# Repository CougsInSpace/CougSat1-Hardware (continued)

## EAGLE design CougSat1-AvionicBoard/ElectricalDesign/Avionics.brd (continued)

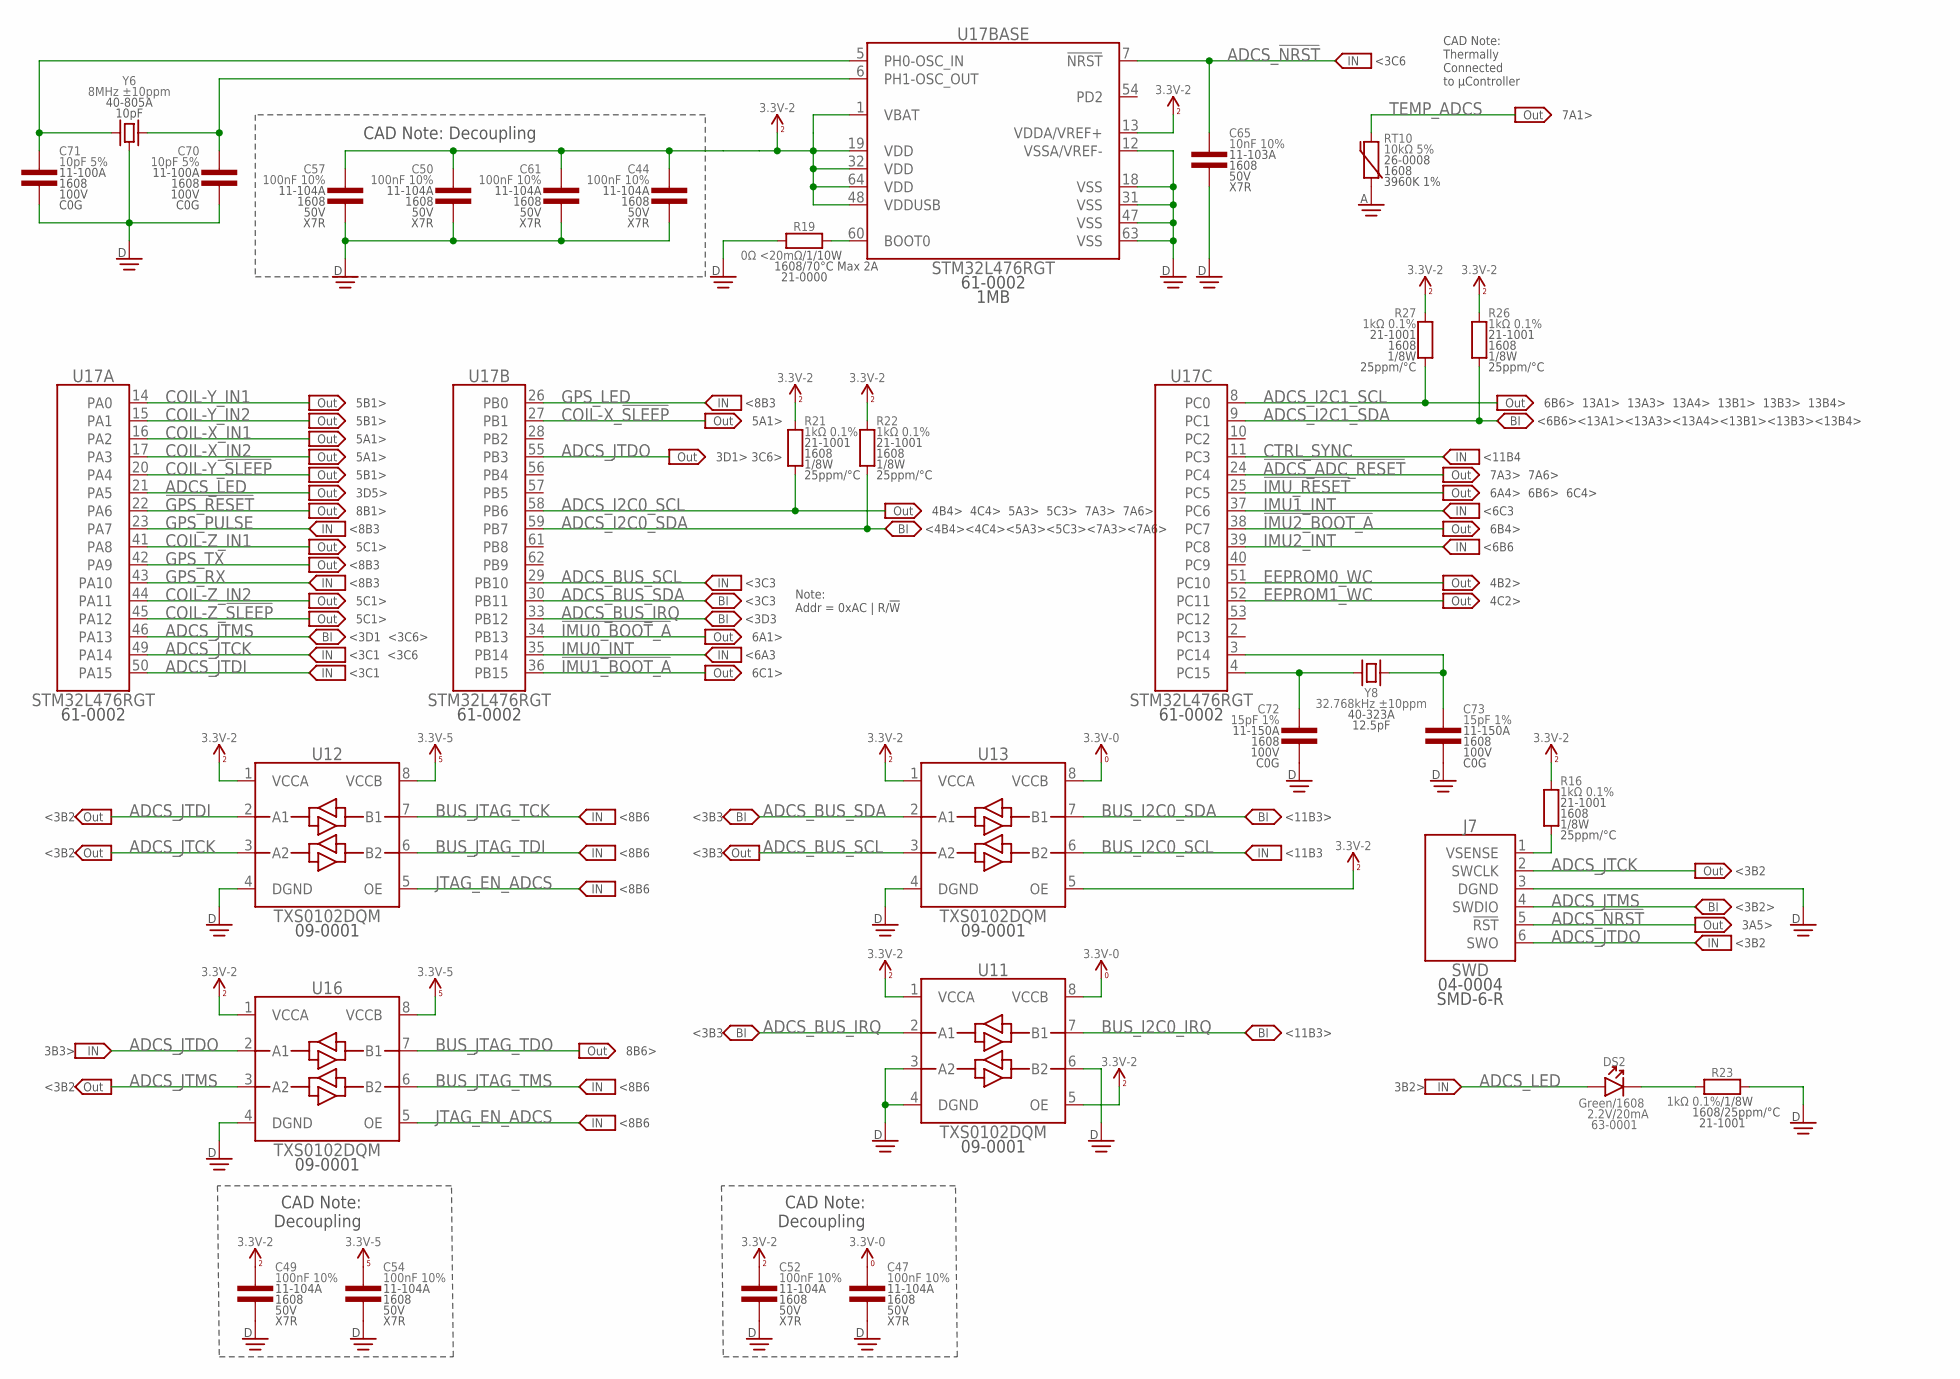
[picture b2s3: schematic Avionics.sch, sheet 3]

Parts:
C44, C47, C49, C50, C52, C54, C57, C61: 100nF 10%; 1608
C65: 10nF 10%; 1608
C70, C71: 10pF 5%; 1608
C72, C73: 15pF 1%; 1608
DS2: Green; 1608-POL
J7: SWD; SMD2.54-1X06-R
R16, R21, R22, R23, R26, R27: 1kΩ 0.1%; 1608
R19: 0Ω <20mΩ; 1608
RT10: 10kΩ 5%; 1608
U11, U12, U13, U16: TXS0102DQM; X2SON-8
U17: STM32L476RGT; QFP-64-1010
Y6: 8MHz ±10ppm; SMD-5032
Y8: 32.768kHz ±10ppm; SMD-3215

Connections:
3.3V_0: C47.1, U11.8 (VCCB), U13.8 (VCCB); also elsewhere on the board
3.3V_2: C44.1, C49.1, C50.1, C52.1, C57.1, C61.1, R16.2, R21.2, R22.2, R26.2, R27.2, U11.1 (VCCA), U11.5 (OE), U12.1 (VCCA), U13.1 (VCCA), U13.5 (OE), U16.1 (VCCA), U17.1 (VBAT), U17.13 (VDDA/VREF+), U17.19 (VDD), U17.32 (VDD), U17.48 (VDDUSB), U17.64 (VDD); also elsewhere on the board
3.3V_5: C54.1, U12.8 (VCCB), U16.8 (VCCB); also elsewhere on the board
!ADCS_ADC_RESET!: U17.24 (PC4); also elsewhere on the board
!GPS_RESET: U17.22 (PA6); also elsewhere on the board
!IMU0_BOOT_A: U17.34 (PB13); also elsewhere on the board
!IMU1_BOOT_A: U17.36 (PB15); also elsewhere on the board
!IMU2_BOOT_A: U17.38 (PC7); also elsewhere on the board
!IMU_RESET: U17.25 (PC5); also elsewhere on the board
ADCS_!NRST: C65.1, J7.5 (!RST), U17.7 (!NRST)
ADCS_BOOT0: R19.2, U17.60 (BOOT0)
ADCS_BUS_IRQ: U11.2 (A1), U17.33 (PB12)
ADCS_BUS_SCL: U13.3 (A2), U17.29 (PB10)
ADCS_BUS_SDA: U13.2 (A1), U17.30 (PB11)
ADCS_I2C0_SCL: R21.1, U17.58 (PB6); also elsewhere on the board
ADCS_I2C0_SDA: R22.1, U17.59 (PB7); also elsewhere on the board
ADCS_I2C1_SCL: R27.1, U17.8 (PC0); also elsewhere on the board
ADCS_I2C1_SDA: R26.1, U17.9 (PC1); also elsewhere on the board
ADCS_JTCK: J7.2 (SWCLK), U12.3 (A2), U17.49 (PA14)
ADCS_JTDI: U12.2 (A1), U17.50 (PA15)
ADCS_JTDO: J7.6 (SWO), U16.2 (A1), U17.55 (PB3)
ADCS_JTMS: J7.4 (SWDIO), U16.3 (A2), U17.46 (PA13)
ADCS_LED: DS2.A, U17.21 (PA5)
ADCS_LED_GND: DS2.C, R23.1
ADCS_OSC_32_IN: C72.1, U17.4 (PC15), Y8.1
ADCS_OSC_32_OUT: C73.1, U17.3 (PC14), Y8.2
ADCS_OSC_IN: C71.1, U17.5 (PH0-OSC_IN), Y6.1
ADCS_OSC_OUT: C70.1, U17.6 (PH1-OSC_OUT), Y6.3 (2)
ADCS_SWD_VSENCE: J7.1 (VSENSE), R16.1
AGND: RT10.1; also elsewhere on the board
BUS_I2C0_IRQ: U11.7 (B1); also elsewhere on the board
BUS_I2C0_SCL: U13.6 (B2); also elsewhere on the board
BUS_I2C0_SDA: U13.7 (B1); also elsewhere on the board
BUS_JTAG_TCK: U12.7 (B1); also elsewhere on the board
BUS_JTAG_TDI: U12.6 (B2); also elsewhere on the board
BUS_JTAG_TDO: U16.7 (B1); also elsewhere on the board
BUS_JTAG_TMS: U16.6 (B2); also elsewhere on the board
COIL-X_!SLEEP: U17.27 (PB1); also elsewhere on the board
COIL-X_IN1: U17.16 (PA2); also elsewhere on the board
COIL-X_IN2: U17.17 (PA3); also elsewhere on the board
COIL-Y_!SLEEP: U17.20 (PA4); also elsewhere on the board
COIL-Y_IN1: U17.14 (PA0); also elsewhere on the board
COIL-Y_IN2: U17.15 (PA1); also elsewhere on the board
COIL-Z_!SLEEP: U17.45 (PA12); also elsewhere on the board
COIL-Z_IN1: U17.41 (PA8); also elsewhere on the board
COIL-Z_IN2: U17.44 (PA11); also elsewhere on the board
CTRL_SYNC: U17.11 (PC3); also elsewhere on the board
DGND: C44.2, C47.2, C49.2, C50.2, C52.2, C54.2, C57.2, C61.2, C65.2, C70.2, C71.2, C72.2, C73.2, J7.3 (DGND), R19.1, R23.2, U11.3 (A2), U11.4 (DGND), U11.6 (B2), U12.4 (DGND), U13.4 (DGND), U16.4 (DGND), U17.12 (VSSA/VREF-), U17.18 (VSS), U17.31 (VSS), U17.47 (VSS), U17.63 (VSS), Y6.2 (GND), Y6.4 (GND); also elsewhere on the board
EEPROM0_WC: U17.51 (PC10); also elsewhere on the board
EEPROM1_WC: U17.52 (PC11); also elsewhere on the board
GPS_LED: U17.26 (PB0); also elsewhere on the board
GPS_PULSE: U17.23 (PA7); also elsewhere on the board
GPS_RX: U17.43 (PA10); also elsewhere on the board
GPS_TX: U17.42 (PA9); also elsewhere on the board
IMU0_INT: U17.35 (PB14); also elsewhere on the board
IMU1_INT: U17.37 (PC6); also elsewhere on the board
IMU2_INT: U17.39 (PC8); also elsewhere on the board
JTAG_EN_ADCS: U12.5 (OE), U16.5 (OE); also elsewhere on the board
TEMP_ADCS: RT10.2; also elsewhere on the board

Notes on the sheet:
5C1>
8B1>
<8B3
3D1> 3C6>
<3B2
<3B2>
4B4> 4C4> 5A3> 5C3> 7A3> 7A6>
<4B4><4C4><5A3><5C3><7A3><7A6>
<11B3>
6A1>
<6A3
6C1>
<6C3
6B4>
<6B6
4B2>
4C2>
6B6> 13A1> 13A3> 13A4> 13B1> 13B3> 13B4>
<6B6><13A1><13A3><13A4><13B1><13B3><13B4>
<3B2
3B3>
<8B6
8B6>
CAD Note: Thermally Connected to µController
7A1>
3A5>
3D5>
3B2>
CAD Note: Decoupling
CAD Note: Decoupling
Note: Addr = 0xAC | R/!W!
<11B4
6A4> 6B6> 6C4>
7A3> 7A6>
<3B3
<3D1 <3C6>
<3C1 <3C6
<3C1
<3C3
<3D3

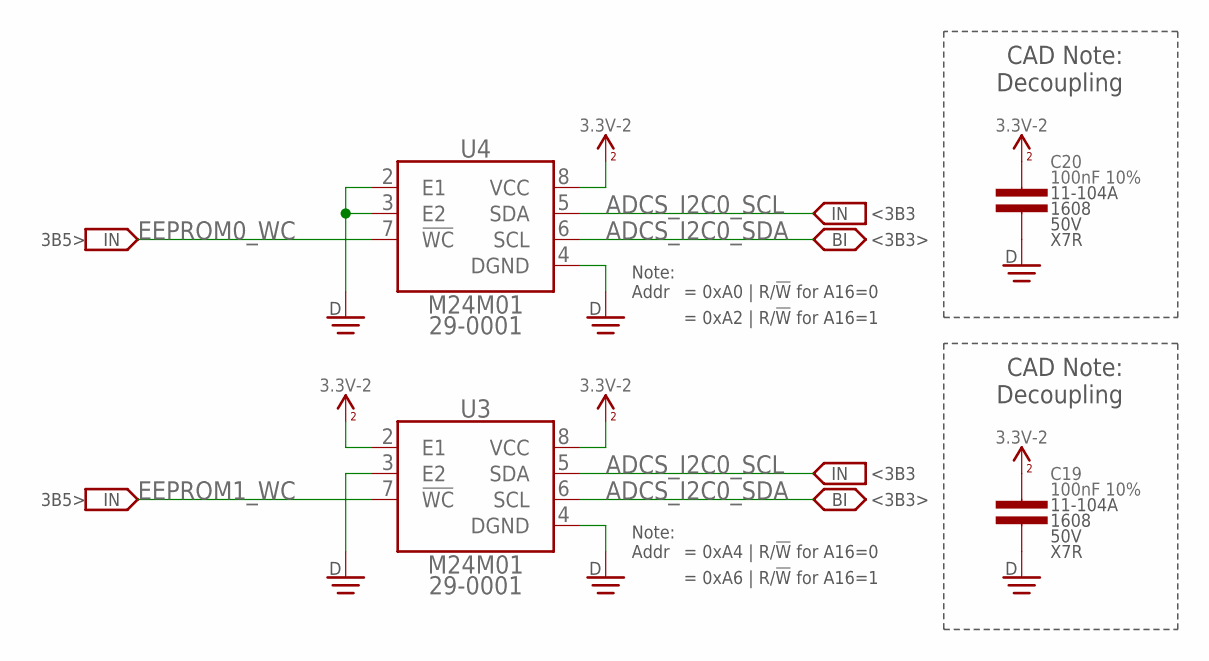
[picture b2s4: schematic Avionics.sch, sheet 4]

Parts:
C19, C20: 100nF 10%; 1608
U3, U4: M24M01; SO8

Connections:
3.3V_2: C19.1, C20.1, U3.2 (E1), U3.8 (VCC), U4.8 (VCC); also elsewhere on the board
ADCS_I2C0_SCL: U3.5 (SDA), U4.5 (SDA); also elsewhere on the board
ADCS_I2C0_SDA: U3.6 (SCL), U4.6 (SCL); also elsewhere on the board
DGND: C19.2, C20.2, U3.3 (E2), U3.4 (DGND), U4.2 (E1), U4.3 (E2), U4.4 (DGND); also elsewhere on the board
EEPROM0_WC: U4.7 (!WC); also elsewhere on the board
EEPROM1_WC: U3.7 (!WC); also elsewhere on the board

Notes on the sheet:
<3B3>
<3B3
3B5>
CAD Note: Decoupling
Note: Addr
= 0xA2 | R/!W! for A16=1
= 0xA0 | R/!W! for A16=0
= 0xA6 | R/!W! for A16=1
= 0xA4 | R/!W! for A16=0

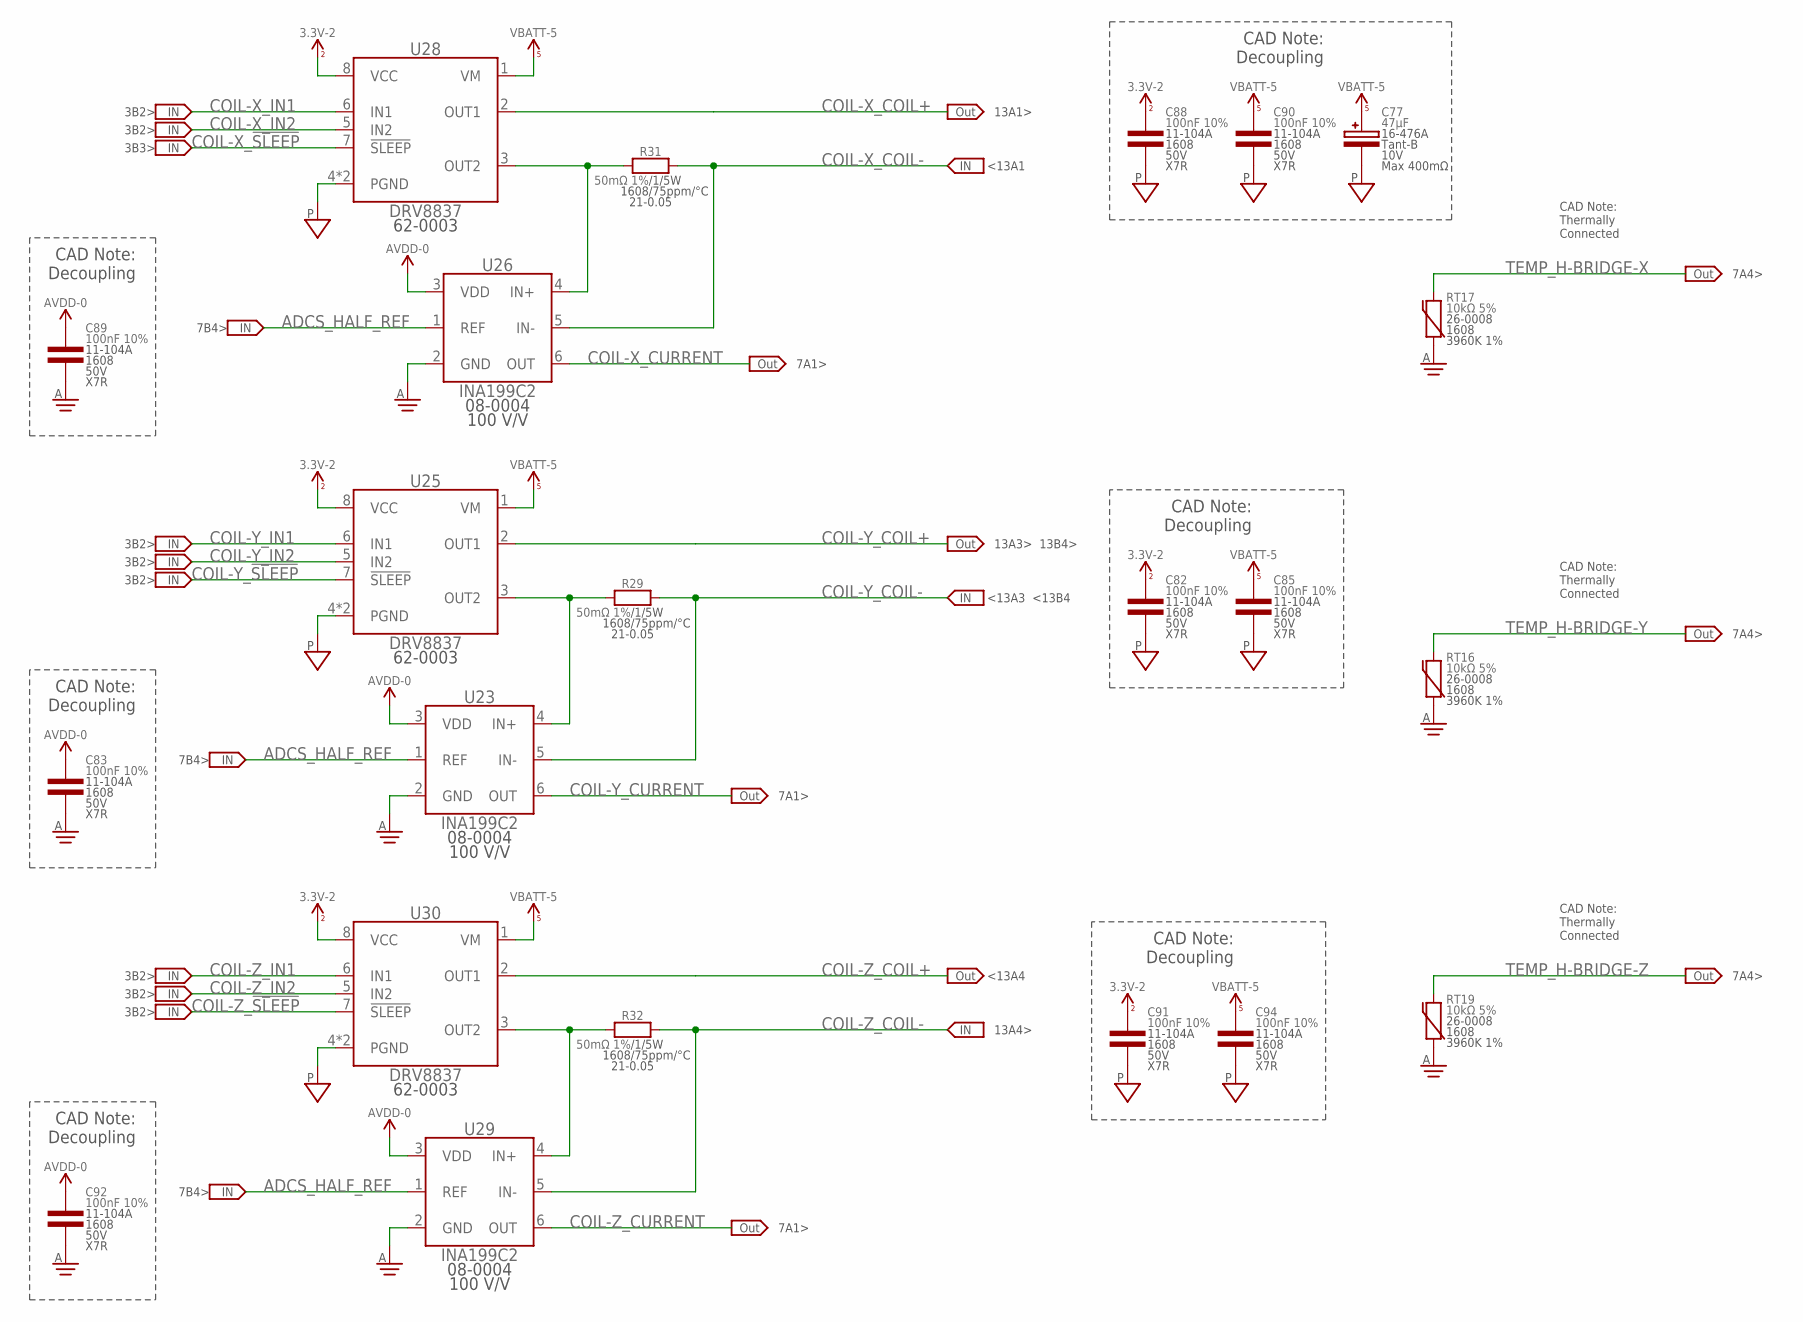
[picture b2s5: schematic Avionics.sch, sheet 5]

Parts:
C77: 47µF; 4028-POL
C82, C83, C85, C88, C89, C90, C91, C92, C94: 100nF 10%; 1608
R29, R31, R32: 50mΩ 1%; 1608
RT16, RT17, RT19: 10kΩ 5%; 1608
U23, U26, U29: INA199C2; SOT363
U25, U28, U30: DRV8837; WSON-8

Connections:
3.3V_2: C82.1, C88.1, C91.1, U25.8 (VCC), U28.8 (VCC), U30.8 (VCC); also elsewhere on the board
ADCS_HALF_REF: U23.1 (REF), U26.1 (REF), U29.1 (REF); also elsewhere on the board
AGND: C83.2, C89.2, C92.2, RT16.1, RT17.1, RT19.1, U23.2 (GND), U26.2 (GND), U29.2 (GND); also elsewhere on the board
AVDD-0: C83.1, C89.1, C92.1, U23.3 (VDD), U26.3 (VDD), U29.3 (VDD); also elsewhere on the board
COIL-X_!SLEEP: U28.7 (!SLEEP); also elsewhere on the board
COIL-X_COIL+: U28.2 (OUT1); also elsewhere on the board
COIL-X_COIL-: R31.2, U26.5 (IN-); also elsewhere on the board
COIL-X_CURRENT: U26.6 (OUT); also elsewhere on the board
COIL-X_IN1: U28.6 (IN1); also elsewhere on the board
COIL-X_IN2: U28.5 (IN2); also elsewhere on the board
COIL-X_OUT2: R31.1, U26.4 (IN+), U28.3 (OUT2)
COIL-Y_!SLEEP: U25.7 (!SLEEP); also elsewhere on the board
COIL-Y_COIL+: U25.2 (OUT1); also elsewhere on the board
COIL-Y_COIL-: R29.2, U23.5 (IN-); also elsewhere on the board
COIL-Y_CURRENT: U23.6 (OUT); also elsewhere on the board
COIL-Y_IN1: U25.6 (IN1); also elsewhere on the board
COIL-Y_IN2: U25.5 (IN2); also elsewhere on the board
COIL-Y_OUT2: R29.1, U23.4 (IN+), U25.3 (OUT2)
COIL-Z_!SLEEP: U30.7 (!SLEEP); also elsewhere on the board
COIL-Z_COIL+: U30.2 (OUT1); also elsewhere on the board
COIL-Z_COIL-: R32.2, U29.5 (IN-); also elsewhere on the board
COIL-Z_CURRENT: U29.6 (OUT); also elsewhere on the board
COIL-Z_IN1: U30.6 (IN1); also elsewhere on the board
COIL-Z_IN2: U30.5 (IN2); also elsewhere on the board
COIL-Z_OUT2: R32.1, U29.4 (IN+), U30.3 (OUT2)
PGND: C77.C, C82.2, C85.2, C88.2, C90.2, C91.2, C94.2, U25.4 (PGND), U25.PAD (PGND), U28.4 (PGND), U28.PAD (PGND), U30.4 (PGND), U30.PAD (PGND); also elsewhere on the board
TEMP_H-BRIDGE-X: RT17.2; also elsewhere on the board
TEMP_H-BRIDGE-Y: RT16.2; also elsewhere on the board
TEMP_H-BRIDGE-Z: RT19.2; also elsewhere on the board
VBATT_5: C77.A, C85.1, C90.1, C94.1, U25.1 (VM), U28.1 (VM), U30.1 (VM); also elsewhere on the board

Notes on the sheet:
CAD Note: Thermally Connected
7A4>
CAD Note: Decoupling
7B4>
7A1>
3B2>
13A1>
<13A1
3B3>
13A3> 13B4>
<13A3 <13B4
13A4>
<13A4

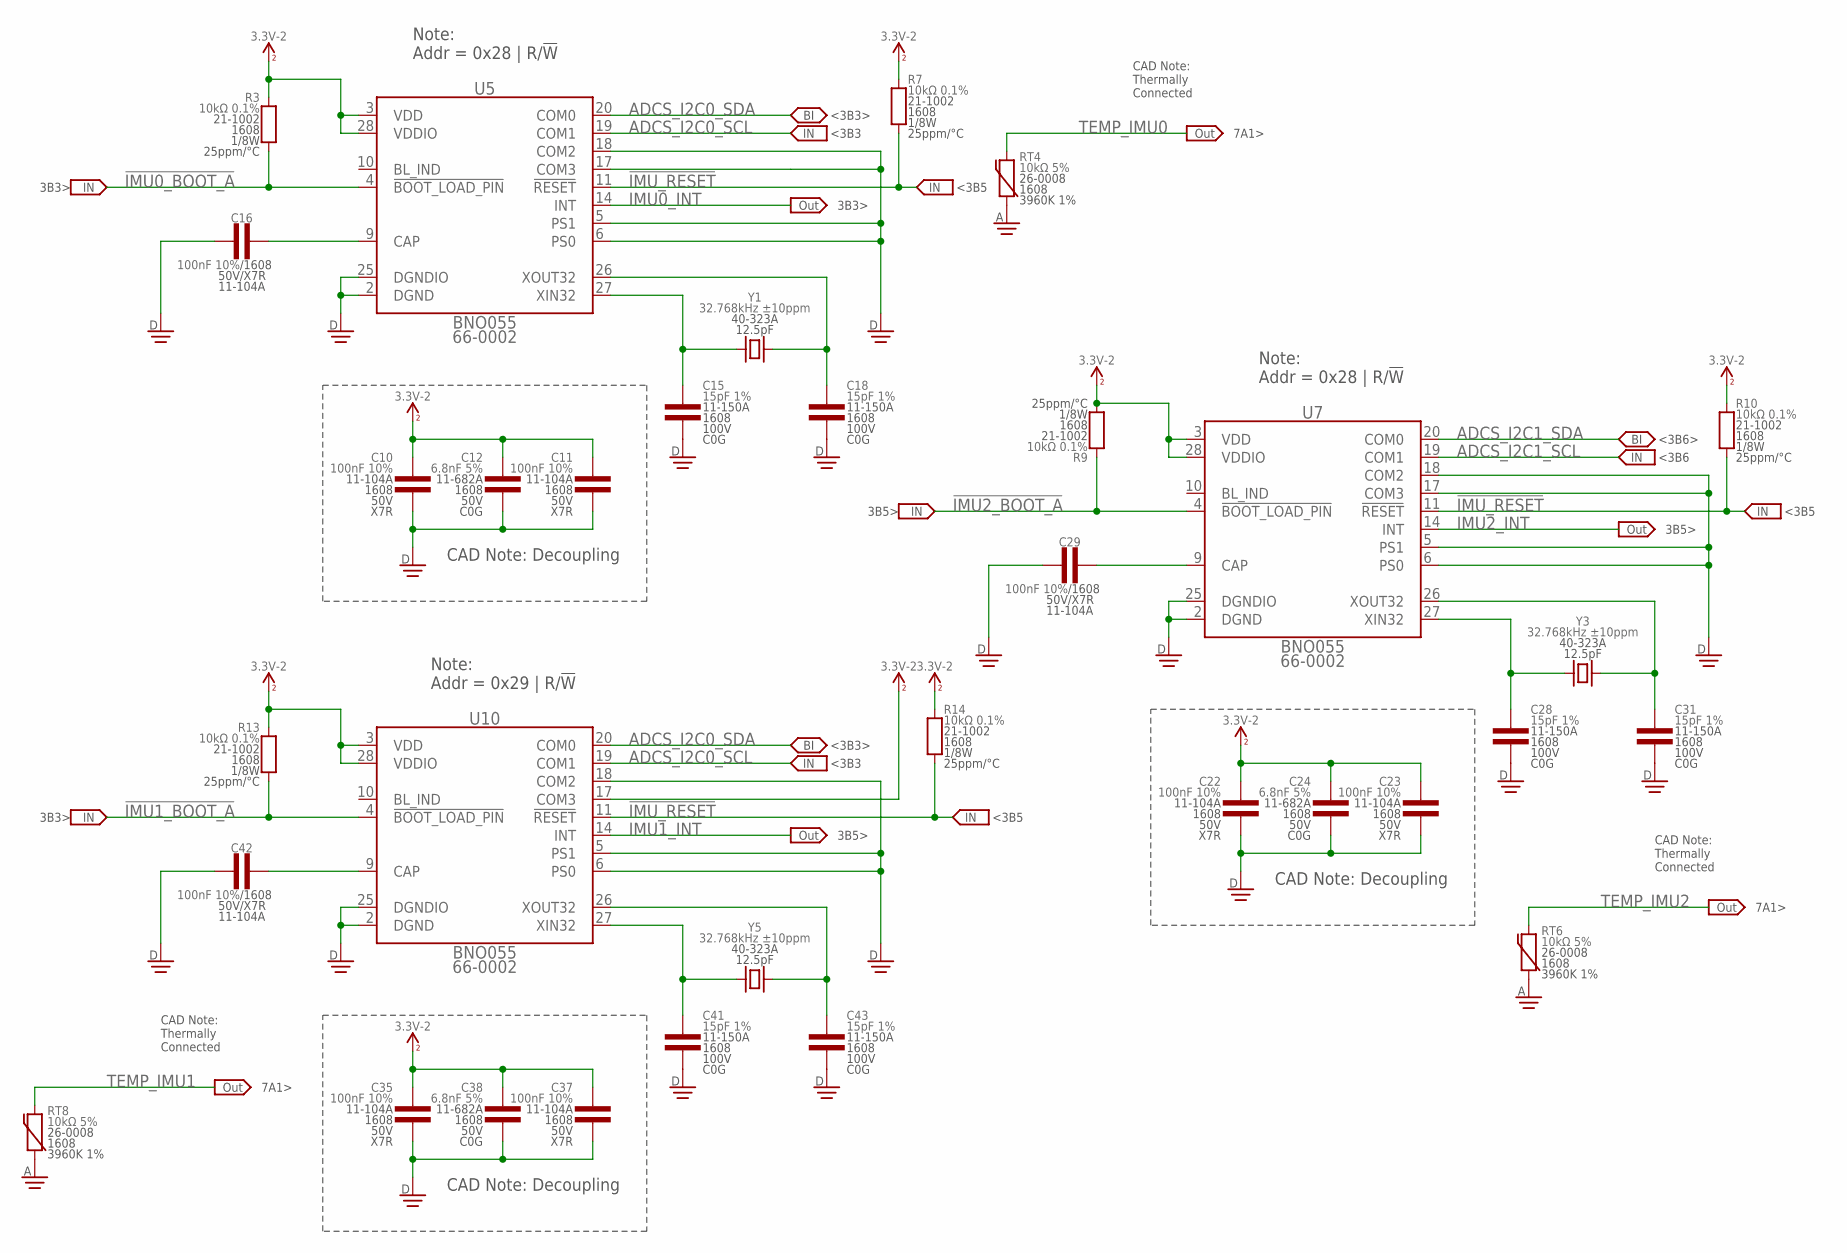
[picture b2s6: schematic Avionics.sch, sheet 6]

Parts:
C10, C11, C16, C22, C23, C29, C35, C37, C42: 100nF 10%; 1608
C12, C24, C38: 6.8nF 5%; 1608
C15, C18, C28, C31, C41, C43: 15pF 1%; 1608
R3, R7, R9, R10, R13, R14: 10kΩ 0.1%; 1608
RT4, RT6, RT8: 10kΩ 5%; 1608
U5, U7, U10: BNO055; LGA-28-4050
Y1, Y3, Y5: 32.768kHz ±10ppm; SMD-3215

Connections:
3.3V_2: C10.1, C11.1, C12.1, C22.1, C23.1, C24.1, C35.1, C37.1, C38.1, R3.2, R7.2, R9.1, R10.2, R13.2, R14.2, U5.3 (VDD), U5.28 (VDDIO), U7.3 (VDD), U7.28 (VDDIO), U10.3 (VDD), U10.17 (COM3), U10.28 (VDDIO); also elsewhere on the board
!IMU0_BOOT_A: R3.1, U5.4 (!BOOT_LOAD_PIN); also elsewhere on the board
!IMU1_BOOT_A: R13.1, U10.4 (!BOOT_LOAD_PIN); also elsewhere on the board
!IMU2_BOOT_A: R9.2, U7.4 (!BOOT_LOAD_PIN); also elsewhere on the board
!IMU_RESET: R7.1, R10.1, R14.1, U5.11 (!RESET), U7.11 (!RESET), U10.11 (!RESET); also elsewhere on the board
ADCS_I2C0_SCL: U5.19 (COM1), U10.19 (COM1); also elsewhere on the board
ADCS_I2C0_SDA: U5.20 (COM0), U10.20 (COM0); also elsewhere on the board
ADCS_I2C1_SCL: U7.19 (COM1); also elsewhere on the board
ADCS_I2C1_SDA: U7.20 (COM0); also elsewhere on the board
ADCS_IMU1_OSC_32_IN: C41.1, U10.27 (XIN32), Y5.2
ADCS_IMU1_OSC_32_IN1: C15.1, U5.27 (XIN32), Y1.2
ADCS_IMU1_OSC_32_IN2: C28.1, U7.27 (XIN32), Y3.2
ADCS_IMU1_OSC_32_OUT: C43.1, U10.26 (XOUT32), Y5.1
ADCS_IMU1_OSC_32_OUT1: C18.1, U5.26 (XOUT32), Y1.1
ADCS_IMU1_OSC_32_OUT2: C31.1, U7.26 (XOUT32), Y3.1
AGND: RT4.1, RT6.1, RT8.1; also elsewhere on the board
DGND: C10.2, C11.2, C12.2, C15.2, C16.1, C18.2, C22.2, C23.2, C24.2, C28.2, C29.1, C31.2, C35.2, C37.2, C38.2, C41.2, C42.1, C43.2, U5.2 (DGND), U5.5 (PS1), U5.6 (PS0), U5.17 (COM3), U5.18 (COM2), U5.25 (DGNDIO), U7.2 (DGND), U7.5 (PS1), U7.6 (PS0), U7.17 (COM3), U7.18 (COM2), U7.25 (DGNDIO), U10.2 (DGND), U10.5 (PS1), U10.6 (PS0), U10.18 (COM2), U10.25 (DGNDIO); also elsewhere on the board
IMU0_CAP: C16.2, U5.9 (CAP)
IMU0_INT: U5.14 (INT); also elsewhere on the board
IMU1_CAP: C42.2, U10.9 (CAP)
IMU1_INT: U10.14 (INT); also elsewhere on the board
IMU2_CAP: C29.2, U7.9 (CAP)
IMU2_INT: U7.14 (INT); also elsewhere on the board
TEMP_IMU0: RT4.2; also elsewhere on the board
TEMP_IMU1: RT8.2; also elsewhere on the board
TEMP_IMU2: RT6.2; also elsewhere on the board

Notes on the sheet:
CAD Note: Decoupling
<3B3>
<3B3
3B3>
3B3>
3B5>
3B5>
<3B6>
<3B6
CAD Note: Thermally Connected
7A1>
Note: Addr = 0x28 | R/!W
Note: Addr = 0x29 | R/!W
<3B5

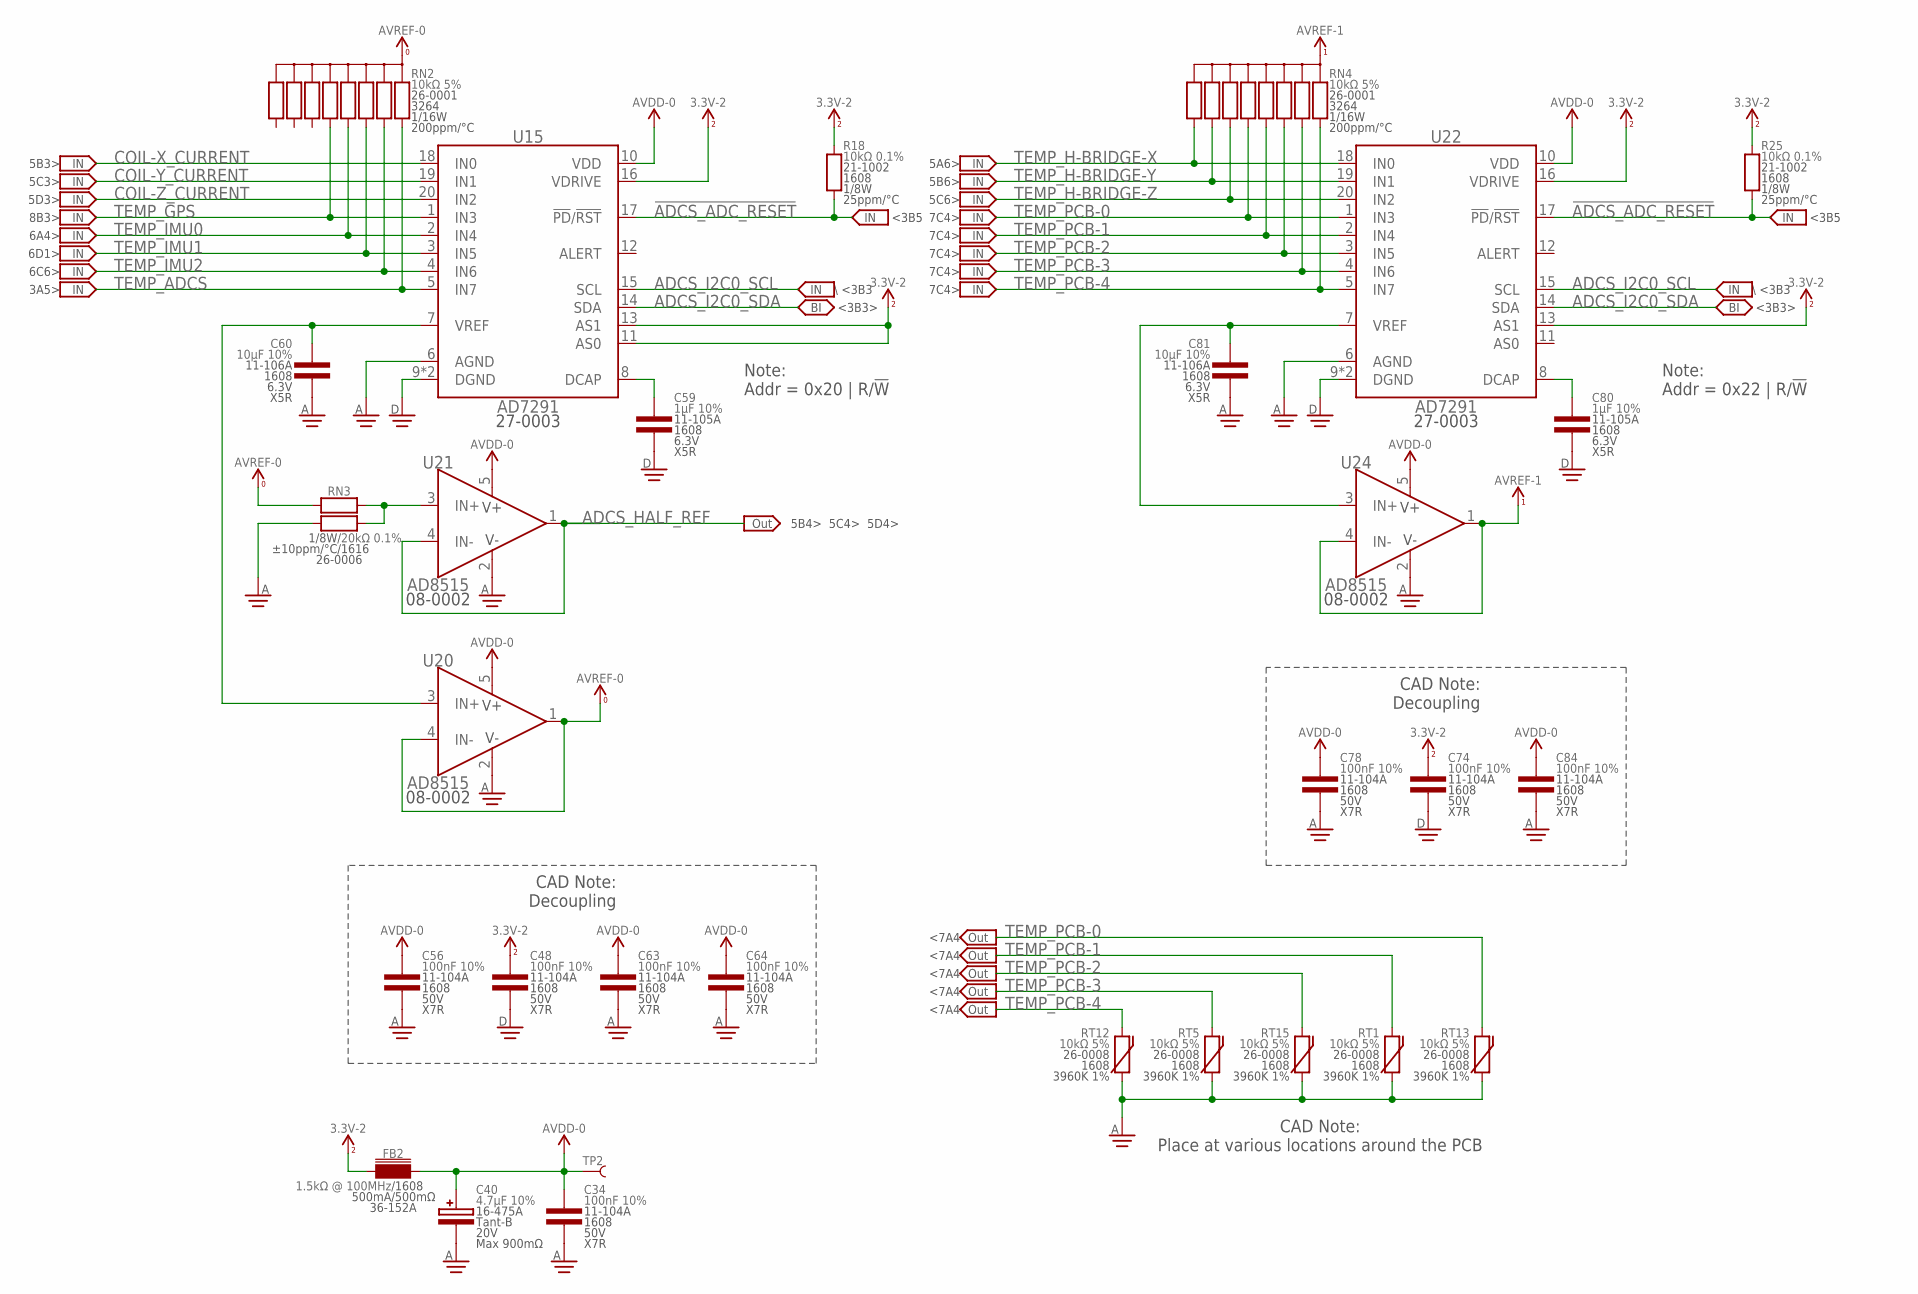
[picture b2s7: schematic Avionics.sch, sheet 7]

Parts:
C34, C48, C56, C63, C64, C74, C78, C84: 100nF 10%; 1608
C40: 4.7µF 10%; 4028-POL
C59, C80: 1µF 10%; 1608
C60, C81: 10µF 10%; 1608
FB2: 1.5kΩ @ 100MHz; 1608
R18, R25: 10kΩ 0.1%; 1608
RN2, RN4: 10kΩ 5%; 3264
RN3: 20kΩ 0.1%; 1616
RT1, RT5, RT12, RT13, RT15: 10kΩ 5%; 1608
TP2: TEST_POINT-SMD-C-1.25; SMD-C-1.25
U15, U22: AD7291; QFN-20-4040
U20, U21, U24: AD8515; SOT23-5

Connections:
3.3V_2: C48.1, C74.1, FB2.1, R18.2, R25.2, U15.11 (AS0), U15.13 (AS1), U15.16 (VDRIVE), U22.13 (AS1), U22.16 (VDRIVE); also elsewhere on the board
!ADCS_ADC_RESET!: R18.1, R25.1, U15.17 (!PD!/!RST), U22.17 (!PD!/!RST); also elsewhere on the board
ADCS_ADC0_DCAP: C59.1, U15.8 (DCAP)
ADCS_ADC0_VREF: C60.1, U15.7 (VREF), U20.3 (IN+)
ADCS_ADC1_DCAP: C80.1, U22.8 (DCAP)
ADCS_ADC1_VREF: C81.1, U22.7 (VREF), U24.3 (IN+)
ADCS_HALF_REF: U21.1 (OUT), U21.4 (IN-); also elsewhere on the board
ADCS_HALF_REF_UNBUFF: RN3.1 (A1), RN3.2 (B1), U21.3 (IN+)
ADCS_I2C0_SCL: U15.15 (SCL), U22.15 (SCL); also elsewhere on the board
ADCS_I2C0_SDA: U15.14 (SDA), U22.14 (SDA); also elsewhere on the board
AGND: C34.2, C40.C, C56.2, C60.2, C63.2, C64.2, C78.2, C81.2, C84.2, RN3.4 (A2), RT1.1, RT5.1, RT12.1, RT13.1, RT15.1, U15.6 (AGND), U20.2 (V-), U21.2 (V-), U22.6 (AGND), U24.2 (V-); also elsewhere on the board
AVDD-0: C34.1, C40.A, C56.1, C63.1, C64.1, C78.1, C84.1, FB2.2, TP2.1, U15.10 (VDD), U20.5 (V+), U21.5 (V+), U22.10 (VDD), U24.5 (V+); also elsewhere on the board
AVREF-0: RN2.5 (C), RN2.10 (C), RN3.3 (B2), U20.1 (OUT), U20.4 (IN-)
AVREF-1: RN4.5 (C), RN4.10 (C), U24.1 (OUT), U24.4 (IN-)
COIL-X_CURRENT: U15.18 (IN0); also elsewhere on the board
COIL-Y_CURRENT: U15.19 (IN1); also elsewhere on the board
COIL-Z_CURRENT: U15.20 (IN2); also elsewhere on the board
DGND: C48.2, C59.2, C74.2, C80.2, U15.9 (DGND), U15.PAD (DGND), U22.9 (DGND), U22.PAD (DGND); also elsewhere on the board
TEMP_ADCS: RN2.1, U15.5 (IN7); also elsewhere on the board
TEMP_GPS: RN2.6 (5), U15.1 (IN3); also elsewhere on the board
TEMP_H-BRIDGE-X: RN4.9 (8), U22.18 (IN0); also elsewhere on the board
TEMP_H-BRIDGE-Y: RN4.8 (7), U22.19 (IN1); also elsewhere on the board
TEMP_H-BRIDGE-Z: RN4.7 (6), U22.20 (IN2); also elsewhere on the board
TEMP_IMU0: RN2.4, U15.2 (IN4); also elsewhere on the board
TEMP_IMU1: RN2.3, U15.3 (IN5); also elsewhere on the board
TEMP_IMU2: RN2.2, U15.4 (IN6); also elsewhere on the board
TEMP_PCB-0: RN4.6 (5), RT13.2, U22.1 (IN3)
TEMP_PCB-1: RN4.4, RT1.2, U22.2 (IN4)
TEMP_PCB-2: RN4.3, RT15.2, U22.3 (IN5)
TEMP_PCB-3: RN4.2, RT5.2, U22.4 (IN6)
TEMP_PCB-4: RN4.1, RT12.2, U22.5 (IN7)

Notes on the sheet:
CAD Note: Decoupling
\ <3B3
<3B3>
5B4> 5C4> 5D4>
5B3>
5C3>
5D3>
8B3>
6A4>
6D1>
6C6>
3A5>
5A6>
5B6>
5C6>
Note: Addr = 0x20 | R/!W
Note: Addr = 0x22 | R/!W
CAD Note: Place at various locations around the PCB
<3B5
7C4>
<7A4

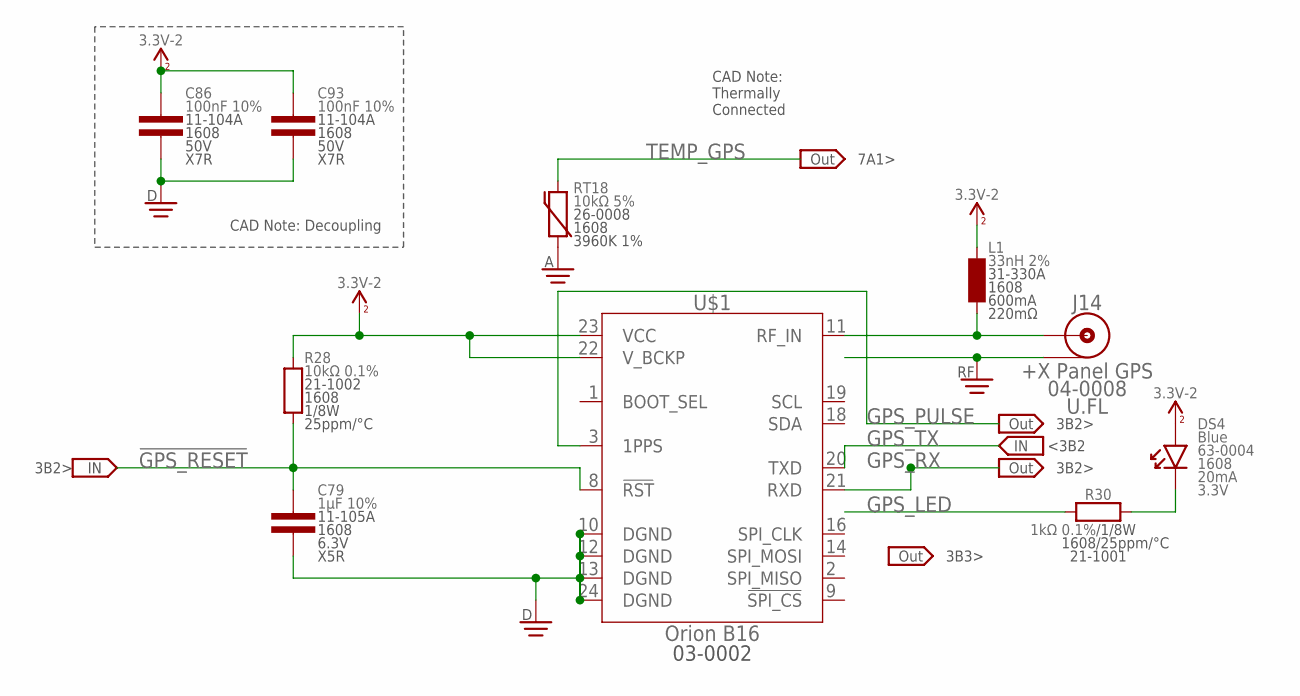
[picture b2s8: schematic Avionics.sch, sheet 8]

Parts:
C79: 1µF 10%; 1608
C86, C93: 100nF 10%; 1608
DS4: Blue; 1608-POL
J14: +X Panel GPS; U.FL
L1: 33nH 2%; 1608
R28: 10kΩ 0.1%; 1608
R30: 1kΩ 0.1%; 1608
RT18: 10kΩ 5%; 1608
U$1: Orion B16; ORION_B16

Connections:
3.3V_2: C86.1, C93.1, DS4.A, L1.2, R28.2, U$1.22 (V_BCKP), U$1.23 (VCC); also elsewhere on the board
!GPS_RESET: C79.1, R28.1, U$1.8 (!RST); also elsewhere on the board
AGND: RT18.1; also elsewhere on the board
DGND: C79.2, C86.2, C93.2, U$1.10 (DGND), U$1.12 (DGND), U$1.13 (DGND), U$1.24 (DGND); also elsewhere on the board
GPS_LED: R30.1; also elsewhere on the board
GPS_LED_DIODE: DS4.C, R30.2
GPS_PULSE: U$1.3 (1PPS); also elsewhere on the board
GPS_RFIN: J14.CENTER, L1.1, U$1.11 (RF_IN)
GPS_RX: U$1.21 (RXD); also elsewhere on the board
GPS_TX: U$1.20 (TXD); also elsewhere on the board
RFGND: J14.SHIELD@1 (SHIELD), J14.SHIELD@2 (SHIELD), J14.SHIELD@13 (SHIELD); also elsewhere on the board
TEMP_GPS: RT18.2; also elsewhere on the board

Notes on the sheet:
CAD Note: Decoupling
3B2>
<3B2
3B3>
3B2>
CAD Note: Thermally Connected
7A1>

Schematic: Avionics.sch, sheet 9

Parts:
C45, C51, C53, C55, C58, C62: 100nF 10%; 1608
C66: 10nF 10%; 1608
C68, C69: 10pF 5%; 1608
C75, C76: 15pF 1%; 1608
DS3: Green; 1608-POL
J1: CougSat Card; CARD-FULL
J8: SWD; SMD2.54-1X06-R
R17, R24: 1kΩ 0.1%; 1608
R20: 0Ω <20mΩ; 1608
RT11: 10kΩ 5%; 1608
U14, U19: TXS0102DQM; X2SON-8
U18: STM32L476RGT; QFP-64-1010
Y7: 8MHz ±10ppm; SMD-5032
Y9: 32.768kHz ±10ppm; SMD-3215

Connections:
3.3V_0: C53.1, U14.8 (VCCB), U19.8 (VCCB); also elsewhere on the board
3.3V_5: C45.1, C51.1, C55.1, C58.1, C62.1, R17.2, U14.1 (VCCA), U14.5 (OE), U18.1 (VBAT), U18.13 (VDDA/VREF+), U18.19 (VDD), U18.32 (VDD), U18.48 (VDDUSB), U18.64 (VDD), U19.1 (VCCA), U19.5 (OE); also elsewhere on the board
AGND: RT11.1; also elsewhere on the board
BUS_JTAG_TCK: J1.A46 (BUS_JTAG_TCK), U18.14 (PA0); also elsewhere on the board
BUS_JTAG_TDI: J1.A47 (BUS_JTAG_TDI), U18.15 (PA1); also elsewhere on the board
BUS_JTAG_TDO: J1.A48 (BUS_JTAG_TDO), U18.16 (PA2); also elsewhere on the board
BUS_JTAG_TMS: J1.A49 (BUS_JTAG_TMS), U18.17 (PA3); also elsewhere on the board
BUS_SPI_IFJR_CS: U14.6 (B2); also elsewhere on the board
BUS_SPI_MISO: U19.6 (B2); also elsewhere on the board
BUS_SPI_MOSI: U14.7 (B1); also elsewhere on the board
BUS_SPI_SCK: U19.7 (B1); also elsewhere on the board
CTRL_SYNC: U18.26 (PB0); also elsewhere on the board
DGND: C45.2, C51.2, C53.2, C55.2, C58.2, C62.2, C66.2, C68.2, C69.2, C75.2, C76.2, J8.3 (DGND), R20.1, R24.2, U14.4 (DGND), U18.12 (VSSA/VREF-), U18.18 (VSS), U18.31 (VSS), U18.47 (VSS), U18.63 (VSS), U19.4 (DGND), Y7.2 (GND), Y7.4 (GND); also elsewhere on the board
IFJR_!NRST: C66.1, J8.5 (!RST), U18.7 (!NRST)
IFJR_BOOT0: R20.2, U18.60 (BOOT0)
IFJR_BUS_CS: U14.2 (A1), U18.24 (PC4)
IFJR_BUS_MISO: U18.22 (PA6), U19.2 (A1)
IFJR_BUS_MOSI: U14.3 (A2), U18.23 (PA7)
IFJR_BUS_SCK: U18.21 (PA5), U19.3 (A2)
IFJR_JTCK: J8.2 (SWCLK), U18.49 (PA14)
IFJR_JTDO: J8.6 (SWO), U18.55 (PB3)
IFJR_JTMS: J8.4 (SWDIO), U18.46 (PA13)
IFJR_LED: DS3.A, U18.20 (PA4)
IFJR_LED_GND: DS3.C, R24.1
IFJR_OSC_32_IN: C76.1, U18.4 (PC15), Y9.1
IFJR_OSC_32_OUT: C75.1, U18.3 (PC14), Y9.2
IFJR_OSC_IN: C68.1, U18.5 (PH0-OSC_IN), Y7.1
IFJR_OSC_OUT: C69.1, U18.6 (PH1-OSC_OUT), Y7.3 (2)
IFJR_SD_CS0: U18.41 (PA8); also elsewhere on the board
IFJR_SD_CS1: U18.43 (PA10); also elsewhere on the board
IFJR_SD_SW0: U18.42 (PA9); also elsewhere on the board
IFJR_SD_SW1: U18.44 (PA11); also elsewhere on the board
IFJR_SPI_MISO: U18.10 (PC2); also elsewhere on the board
IFJR_SPI_MOSI: U18.11 (PC3); also elsewhere on the board
IFJR_SPI_SCK: U18.29 (PB10); also elsewhere on the board
IFJR_SWD_VSENSE: J8.1 (VSENSE), R17.1
JTAG_EN-2: J1.B48 (BUS_JTAG_EN-2), U18.38 (PC7)
JTAG_EN-3: J1.B49 (BUS_JTAG_EN-3), U18.39 (PC8)
JTAG_EN_ADCS: J1.B46 (BUS_JTAG_EN-0), U18.8 (PC0); also elsewhere on the board
JTAG_EN_IHU: J1.B47 (BUS_JTAG_EN-1), U18.9 (PC1); also elsewhere on the board
PR_3.3V-1: J1.A2 (PR_3.3V-1), J1.B2 (PR_3.3V-1)
PR_3.3V-3: J1.A4 (PR_3.3V-3), J1.B4 (PR_3.3V-3)
PR_3.3V-4: J1.A5 (PR_3.3V-4), J1.B5 (PR_3.3V-4)
PR_3.3V-6: J1.A7 (PR_3.3V-6), J1.B7 (PR_3.3V-6)
PR_3.3V-7: J1.A8 (PR_3.3V-7), J1.B8 (PR_3.3V-7)
PR_3.3V-8: J1.A9 (PR_3.3V-8), J1.B9 (PR_3.3V-8)
PR_3.3V-9: J1.A10 (PR_3.3V-9), J1.B10 (PR_3.3V-9)
PR_3.3V-10: J1.A11 (PR_3.3V-10), J1.B11 (PR_3.3V-10)
PR_3.3V-11: J1.A12 (PR_3.3V-11), J1.B12 (PR_3.3V-11)
PR_3.3V-12: J1.A13 (PR_3.3V-12), J1.B13 (PR_3.3V-12)
PR_BATT-0: J1.A14 (PR_BATT-0), J1.B14 (PR_BATT-0)
PR_BATT-1: J1.A15 (PR_BATT-1), J1.B15 (PR_BATT-1)
PR_BATT-2: J1.A16 (PR_BATT-2), J1.B16 (PR_BATT-2)
PR_BATT-3: J1.A17 (PR_BATT-3), J1.B17 (PR_BATT-3)
PR_BATT-4: J1.A18 (PR_BATT-4), J1.B18 (PR_BATT-4)
PR_BATT-6: J1.A20 (PR_BATT-6), J1.B20 (PR_BATT-6)
TEMP_IFJR: RT11.2; also elsewhere on the board

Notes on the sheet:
9B6>
<9B6>
<9B6
<9B2
9B2>
<9B2>
<9B4
<9C6
<9C6>
9C6>
9C2>
<9C2>
<9B3
9A5>
<11B4
CAD Note: Decoupling
9B2>
CAD Note: Thermally Connected
12C1>
9B4>
<9C1
9C1>
<9D1
10B4>
<10B4
10C4>
<10C4
<11B2
11B2>
<9B2
CAD Note: Decoupling
<9B4

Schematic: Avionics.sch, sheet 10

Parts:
C67, C87: 100nF 10%; 1608
J12: IFJR SD0; µSD-PUSH-PUSH
J13: iFJR SD1; µSD-PUSH-PUSH
RT9, RT14: 10kΩ 5%; 1608

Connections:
3.3V_5: C67.1, C87.1, J12.VDD, J13.VDD; also elsewhere on the board
AGND: RT9.1, RT14.1; also elsewhere on the board
DGND: C67.2, C87.2, J12.SW-LEVER (SW-), J12.VSS, J13.SW-LEVER (SW-), J13.VSS; also elsewhere on the board
IFJR_SD_CS0: J12.CD/DAT3; also elsewhere on the board
IFJR_SD_CS1: J13.CD/DAT3; also elsewhere on the board
IFJR_SD_SW0: J12.SW (SW+); also elsewhere on the board
IFJR_SD_SW1: J13.SW (SW+); also elsewhere on the board
IFJR_SPI_MISO: J12.DAT0, J13.DAT0; also elsewhere on the board
IFJR_SPI_MOSI: J12.CMD, J13.CMD; also elsewhere on the board
IFJR_SPI_SCK: J12.CLK, J13.CLK; also elsewhere on the board
TEMP_SD_IFJR0: RT9.2; also elsewhere on the board
TEMP_SD_IFJR1: RT14.2; also elsewhere on the board

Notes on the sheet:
CAD Note: Decoupling
<10B4
<10B3
10B4>
10B2>
<10B2
CAD Note: Thermally Connected
12C1>
12C1>
